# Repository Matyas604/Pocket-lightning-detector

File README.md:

# Pocket lightning detector
A while back, I was browsing websites with various components and modules when a lightning sensor cought my eye. I was really curious about how it works, so I started researching it. After watching a few Youtube videos 
about this module, I decided I had to try it out. Then I started thinking, and suddenly occurred to me that it would be really cool to create a small, portable, battery-powered device that fits in your pocket and detect 
lightnings. So why not? Why not just design my own PCB and build the entire device myself?

I really enjoyd this project because I tried out a lot of different thigs: studying datasheets and schematics, searching for and creating my own schematic, and designing the PCB and case.

## Features
- The entire device is powered by a **Li-Po** rechargeable battery
- It uses the [**ESP-C3-MINI**](https://documentation.espressif.com/esp32-c3-mini-1_datasheet_en.pdf) as the main microcontroller
- Has **USB-C** port for programming and charging the device
- [**AS3935**](https://www.laskakit.cz/user/related_files/as3935_datasheet.pdf) and **MA5532-AE** for lightning detection
- Detects lightning strikes up to **40 km** away
- Records the distance, energy and current time of lightning strike
- Everything is stored in the internal **RTC memory**, which can store up to 50 lightnings strikes
- Communicates with a mobile via **Bluetooth** to synchronize the time and data
- Has audio feedback when a lightning strike been detected or other thing happened
- Various battery protections, such as **overcharge**, **undercharge**, **over-discharge** and **overvoltage**
- It uses deep sleep mode to get the longest possible battery life

## CAD model
Everything is stored in a case consisting of two parts: a base and a top cover. The top cover is secured with four **M3** screws and heat inserts, along with the **PCB**, which is secured with two screws. The buttons are labeled
with icons for clear identification of their functions. The dimensions are 106 mm in length, 60 mm in width, and 35 mm in height.

<p align="center">
  <strong>Made in Fusion360</strong>
</p>

## PCB
It includes two switches: one to turn on and of the device and other to activate **Bluetooth**. In the upper right corner, above the **USB-C** port, are chips for charging, protection, monitoring, and drawing power from the battery, there is also a connector for the battery. The lightning sensor communicates via **I2C**. The pull-up resistors are located under the **ESP-32** near the edge of the **PCB**. The dimensions of **PCB** are 99.7 mm x 35 mm.

<p align="center">
  Schematic
</p>

<p align="center">
  PCB
</p>

<p align="center">
  <strong>Made in KiCad</strong>
</p>
⚠️ The area around the lightning sensor antenna must be kept sufficiently far away from metal parts, as there could interfere with the antenna. For this reason, there si no GND copper area around it, and no screws are located nerby.

## Poster

<p align="center">
  <strong>Made in Figma</strong>
</p>

## Firmware
It uses standard **C++** code. One button turns the device on, and the other activates **Bluetooth** to display lightnings data and synchronize the time. The time must be synchronized every time the device is turned on. Data cen be currently displayed via a serial monitor application. Once the device is connected, it automatically sends lightning data every 3 seconds. Time is synchronized by sending a command, and the board then retrieves the current time. Lightning strikes and the time are stored in **RTC memory**, so they are erased when the device is turned off. The device runs continuously in deep sleep mode and wakes up only when a lightning strike occurs to save data about the strike and the time it happened, then goes back into deep sleep. **RTC memory** is the only component that remains active even when the device is in deep sleep mode. The **RTC memory** stores a maximum of the last **50 lightning strikes** to prevent it from becoming overloaded. My goal was to maximize battery life, so I chose **Bluetooth** over **Wi-Fi** because **Bluetooth** is much more power-efficient, and I use deep sleep mode as well (Once the device is finished, I’ll carefully measure its battery life).  You can found further details in the comments within the code. After i finished the device, I’ll probably create a nice app where the lightnings will be saved and can be viewed back in time. 

## BOM
You can find it in .csv format [here](https://github.com/Matyas604/Pocket-lightning-detector/blob/main/BOM.csv). 

## License
This project is licensed under the GNU GPL v3.
```
Matyas604/Pocket-lightning-detector - Battery-powered Pocket Lightning Detector
Copyright (C) 2026 Matyáš Caha

This program is free software: you can redistribute it and/or modify
it under the terms of the GNU General Public License as published by
the Free Software Foundation, either version 3 of the License, or
(at your option) any later version.

This program is distributed in the hope that it will be useful,
but WITHOUT ANY WARRANTY; without even the implied warranty of
MERCHANTABILITY or FITNESS FOR A PARTICULAR PURPOSE. See the
GNU General Public License for more details.

You should have received a copy of the GNU General Public License
along with this program. If not, see <https://www.gnu.org/licenses/>.
```

<hr>

<p align="center">
  Made with ❤️ by <a href="https://github.com/Matyas604">@Matyas604</a>
</p>

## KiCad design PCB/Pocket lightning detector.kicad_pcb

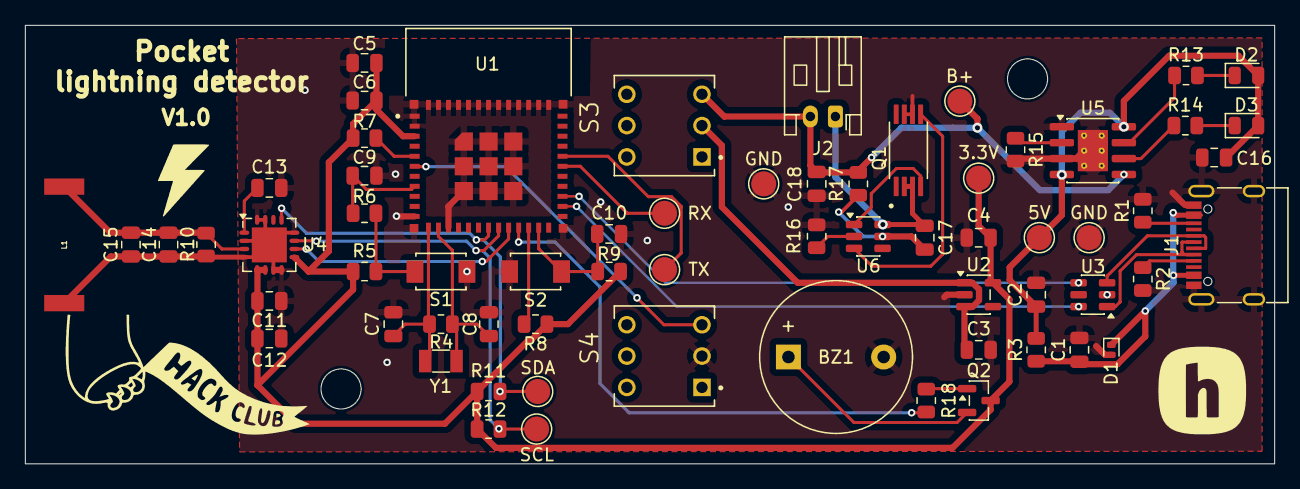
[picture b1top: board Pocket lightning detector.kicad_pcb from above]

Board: 2 copper layers, 99.7 x 35.0 mm, 65 parts (0 on the bottom side), 40 nets.

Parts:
3.3V: 3.3V; TestPoint_Pad_D2.0mm
5V: 5V; TestPoint_Pad_D2.0mm
B+: OUT+; TestPoint_Pad_D2.0mm
BZ1: Buzzer; Buzzer_12x9.5RM7.6
C1, C2: 4uF; C_0805_2012Metric
C3, C4: 4.7uF; C_0805_2012Metric
C5, C9, C10, C11: 100nF; C_0805_2012Metric
C6: 22uF; C_0805_2012Metric
C7, C8: TBD; C_0805_2012Metric
C12: 1uF; C_0805_2012Metric
C13, C18: 10uF; C_0805_2012Metric
C14, C15: 470pF; C_0805_2012Metric
C16, C17: 0.1uF; C_0805_2012Metric
D1: PESD5V0L1ULD; D_SOD-882D
D2: LED Red; LED_0805_2012Metric
D3: LED Blue; LED_0805_2012Metric
GND: GND; TestPoint_Pad_D2.0mm
GND#2: OUT-; TestPoint_Pad_D2.0mm
J1: USB_C_Receptacle_USB2.0_16P; USB_C_Receptacle_G-Switch_GT-USB-7010ASV
J2: Conn_01x02_Pin; JST_PH_S2B-PH-K_1x02_P2.00mm_Horizontal
L1: 100uH; MA5532-AE
Q1: FS8205A; SOP65P640X120-8N
Q2: SS8550; SOT-23
R1, R2, R11, R12: 5.1k; R_0805_2012Metric
R3: 0R; R_0805_2012Metric
R4: TBD; R_0805_2012Metric
R5, R7, R8, R9, R10: 10k; R_0805_2012Metric
R6, R17: 100R; R_0805_2012Metric
R13, R14, R16, R18: 1k; R_0805_2012Metric
R15: 1.2k; R_0805_2012Metric
RX: RX; TestPoint_Pad_D2.0mm
S1, S2: TS-1088-AR02016; SW_TS-1088-AR02016
S3, S4: TL2285EE; SW_TL2285EE
SCL: SCL; TestPoint_Pad_D2.0mm
SDA: SDA; TestPoint_Pad_D2.0mm
TX: TX; TestPoint_Pad_D2.0mm
U1: ESP32-C3-MINI-1-N4; XCVR_ESP32-C3-MINI-1-N4
U2: AP2112K-3.3; SOT-23-5
U3: USBLC6-2SC6; SOT-23-6
U4: AS3935; MLPQ-16-1EP_4x4mm_P0.65mm_EP2.8x2.8mm
U5: TP4056-42-ESOP8; SOIC-8-1EP_3.9x4.9mm_P1.27mm_EP2.41x3.3mm_ThermalVias
U6: DW01A; SOT-23-6
Y1: Crystal; Crystal_SMD_3215-2Pin_3.2x1.5mm

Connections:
+3.3V: 3.3V.1, C4.1, C5.1, C6.1, C11.2, C12.2, Q2.3 (C), R5.1, R7.2, R8.2, R9.1, R11.1, R12.1, U1.3 (3V3), U2.5 (VOUT), U4.5 (Vdd), U4.6 (VReg), U4.9 (SI)
+5V: 5V.1, C2.1, C16.1, D2.2 (A), D3.2 (A), R3.2, U5.4 (V_{CC}), U5.8 (CE)
B+: B+.1, C18.1, J2.2, R17.1, S3.3, U5.5 (BAT)
B-: C17.1, J2.1, Q1.2, Q1.3, U6.6 (GND)
BOOT: C10.1, R9.2, S2.2, U1.23 (IO9)
BUZZ: R18.1, U1.21 (IO7)
D+: U1.27 (IO19), U3.4 (I/O2)
D-: U1.26 (IO18), U3.6 (I/O1)
EN: C9.1, R6.1, U1.8 (EN)
IRQ: U1.20 (IO6), U4.10 (IRQ)
unnamed: BZ1.1 (+), Q2.2 (E)
unnamed: D2.1 (K), R13.2
unnamed: D3.1 (K), R14.2
unnamed: J1.A5 (CC1), R2.1
unnamed: J1.B5 (CC2), R1.1
unnamed: J1.A6 (D+), J1.B6 (D+), U3.3 (I/O2)
unnamed: J1.A7 (D-), J1.B7 (D-), U3.1 (I/O1)
unnamed: Q2.1 (B), R18.2
unnamed: R5.2, R6.2, S1.2
unnamed: C7.1, R4.1, U1.12 (IO0), Y1.1
unnamed: C8.1, R4.2, U1.13 (IO1), Y1.2
unnamed: R7.1, U1.5 (IO2)
unnamed: R8.1, U1.22 (IO8)
unnamed: RX.1, U1.30 (RXD0)
unnamed: TX.1, U1.31 (TXD0)
unnamed: C13.1, U4.1 (ACG)
unnamed: C14.2, C15.2, L1.1, R10.2, U4.3 (IN+)
unnamed: R15.1, U5.2 (PROG)
unnamed: R13.1, U5.7 (~CHRG)
unnamed: R14.1, U5.6 (~STDBY)
unnamed: R16.2, U6.2 (CS)
unnamed: Q1.5, U6.3 (OC)
unnamed: Q1.4, U6.1 (OD)
unnamed: C17.2, R17.2, U6.5 (VCC)
OUT-: BZ1.2 (-), C1.2, C2.2, C3.2, C4.2, C5.2, C6.2, C7.2, C8.2, C9.2, C10.2, C11.1, C12.1, C13.2, C14.1, C15.1, C16.2, C18.2, D1.2 (A), GND.1, GND#2.1, J1.A1 (GND), J1.A12 (GND), J1.B1 (GND), J1.B12 (GND), J1.S1 (SHIELD), L1.2, Q1.6, Q1.7, R1.2, R2.2, R10.1, R15.2, R16.1, S1.1, S2.1, S4.2, U1.1 (GND), U1.2 (GND), U1.11 (GND), U1.14 (GND), U1.36 (GND), U1.37 (GND), U1.38 (GND), U1.39 (GND), U1.40 (GND), U1.41 (GND), U1.42 (GND), U1.43 (GND), U1.44 (GND), U1.45 (GND), U1.46 (GND), U1.47 (GND), U1.48 (GND), U1.49_1 (GND), U1.49_2 (GND), U1.49_3 (GND), U1.49_4 (GND), U1.49_5 (GND), U1.49_6 (GND), U1.49_7 (GND), U1.49_8 (GND), U1.49_9 (GND), U1.50 (GND), U1.51 (GND), U1.52 (GND), U1.53 (GND), U2.2 (GND), U3.2 (GND), U4.2 (IN-), U4.4 (GND), U4.7 (EN), U4.8 (CS), U4.12 (MISO), U4.15 (AD0), U4.16 (AD1), U4.17 (GNDPAD), U5.1 (TEMP), U5.3 (GND), U5.9 (EPAD)
REG+: C3.1, S3.2, U2.1 (VIN), U2.3 (EN)
SCL: R12.2, SCL.1, U1.19 (IO5), U4.11 (SCL)
SDA: R11.2, SDA.1, U1.18 (IO4), U4.13 (MOSI/SDA)
SW: S4.3, U1.6 (IO3)
VBUS: C1.1, D1.1 (K), J1.A4 (VBUS), J1.A9 (VBUS), J1.B4 (VBUS), J1.B9 (VBUS), R3.1

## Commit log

2026-05-15 Adding files
2026-05-16 Add BOM.csv with initial component list
2026-05-17 BOM components update
2026-05-17 BOM fix
2026-05-17 Final BOM fix
2026-05-19 README update
    Added project description and features for the Pocket lightning detector.
2026-05-19 Adding pictures
2026-05-19 README finished!
2026-05-21 Adding Zine
2026-05-22 Final fix schematic
2026-05-22 Final CAD
2026-05-22 BOM done!
2026-05-22 Poster final
2026-05-22 Fixing PCB
2026-05-22 README done!
2026-05-22 Final fix
2026-05-22 Add GNU GPL v3 license
    Added the GNU General Public License version 3 to the project.
2026-05-22 Update README with license
